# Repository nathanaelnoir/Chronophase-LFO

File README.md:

# Chronophase LFO

Chronophase LFO is a clock-synced Eurorack modulation source with an Arduino Nano core, four front-panel controls, one clock input, and separate unipolar, bipolar, and inverted bipolar outputs.

## Contents

- Overview
- Features
- Quick start (KiCad 9)
- Files
- Build & assembly notes
- Testing
- License & contributing

## Overview

This repository contains the KiCad 9 design files for Chronophase LFO, a clocked modulation module for Eurorack. An external clock drives the LFO core, the four main controls adjust `WAVEFORM`, `AMP`, `PHASE`, and `MODULATION`, and the output stage provides `UP_Out`, `BP_Out`, and `BP_Inv_Out` on separate jacks.

The current KiCad 9 project files are named `Synced_LFO`, and the top-level schematic title block still says `Clocked Modulation LFO`. The current documented revision for both the schematic and PCB is `v1.1`.

The hardware clearly includes an `Arduino_Nano_v3.x`, but there is no firmware source in this repository at the moment, only the hardware design files.

## Features

- Clock-synced LFO built around an `Arduino_Nano_v3.x` core and `TL072` output / shaping stages.
- Four front-panel controls: `WAVEFORM`, `AMP`, `PHASE`, and `MODULATION`.
- External `CLK In` jack for sync / clock input.
- Separate `UP_Out`, `BP_Out`, and `BP_Inv_Out` outputs.
- Front-panel activity LED.
- Standard Eurorack power distribution with `+12 V / -12 V / +5 V / GND` through a 16-pin Eurorack header sheet.
- Mixed build: SMD passives, diodes, electrolytics, and SOIC op-amps, with through-hole jacks, pots, LED, and Arduino Nano.

## Quick start

1. Install KiCad 9.
2. Open the project: `KiCad/Synced_LFO.kicad_pro`.
3. Review the top-level schematic and the `EURORACK_POWER` sheet, then run ERC/DRC before exporting manufacturing files.

## Files

- `KiCad/Synced_LFO.kicad_sch` - top-level schematic
- `KiCad/eurorack_power.kicad_sch` - Eurorack power sheet
- `KiCad/Synced_LFO.kicad_pcb` - PCB
- `KiCad/Synced_LFO.kicad_pro` - KiCad 9 project file
- `KiCad/Synced_LFO.kicad_prl` - local KiCad 9 project state
- `KiCad/Synced_LFO.sch` - legacy schematic file
- `KiCad/Synced_LFO.pro` - legacy project file

Note: there is a single PCB layout file (`KiCad/Synced_LFO.kicad_pcb`) for this project.

## Build & assembly notes

- Check orientation on the `Arduino_Nano_v3.x` module before soldering headers or the board directly. The USB end and pin order matter.
- Confirm pin-1 orientation on the `TL072` packages and polarity on the diodes and electrolytics before powering the board.
- Double-check the Eurorack power header orientation before applying power. This design uses `+12 V`, `-12 V`, `+5 V`, and `GND`, so a reversed cable is an easy way to damage parts.
- Panel hardware is straightforward but still substantial: four 100 k pots, four 3.5 mm jacks, and one LED.
- This is a mixed SMD + THT build, so it makes sense to solder the low-profile SMD parts first and leave the pots, jacks, LED, and Nano for later.

## Testing

1. Power the module from a current-limited Eurorack supply and verify `+12 V`, `-12 V`, `+5 V`, and `GND` on the power section before checking the rest of the circuit.
2. Feed a known clock into `CLK In` and confirm the front-panel LED shows activity.
3. Probe `UP_Out`, `BP_Out`, and `BP_Inv_Out` on a scope and confirm all three outputs are present and distinct.
4. Turn `WAVEFORM`, `AMP`, `PHASE`, and `MODULATION` through their full range and verify the outputs respond as expected.
5. If the Arduino Nano is fitted, confirm the module behavior is stable across different clock rates and after power-cycling.

## License & contributing

No `LICENSE` file has been added to this repository yet. Until that changes, assume the design is shared for reference, not under an explicit open-source license.

If a license is added later, this section can be updated properly.

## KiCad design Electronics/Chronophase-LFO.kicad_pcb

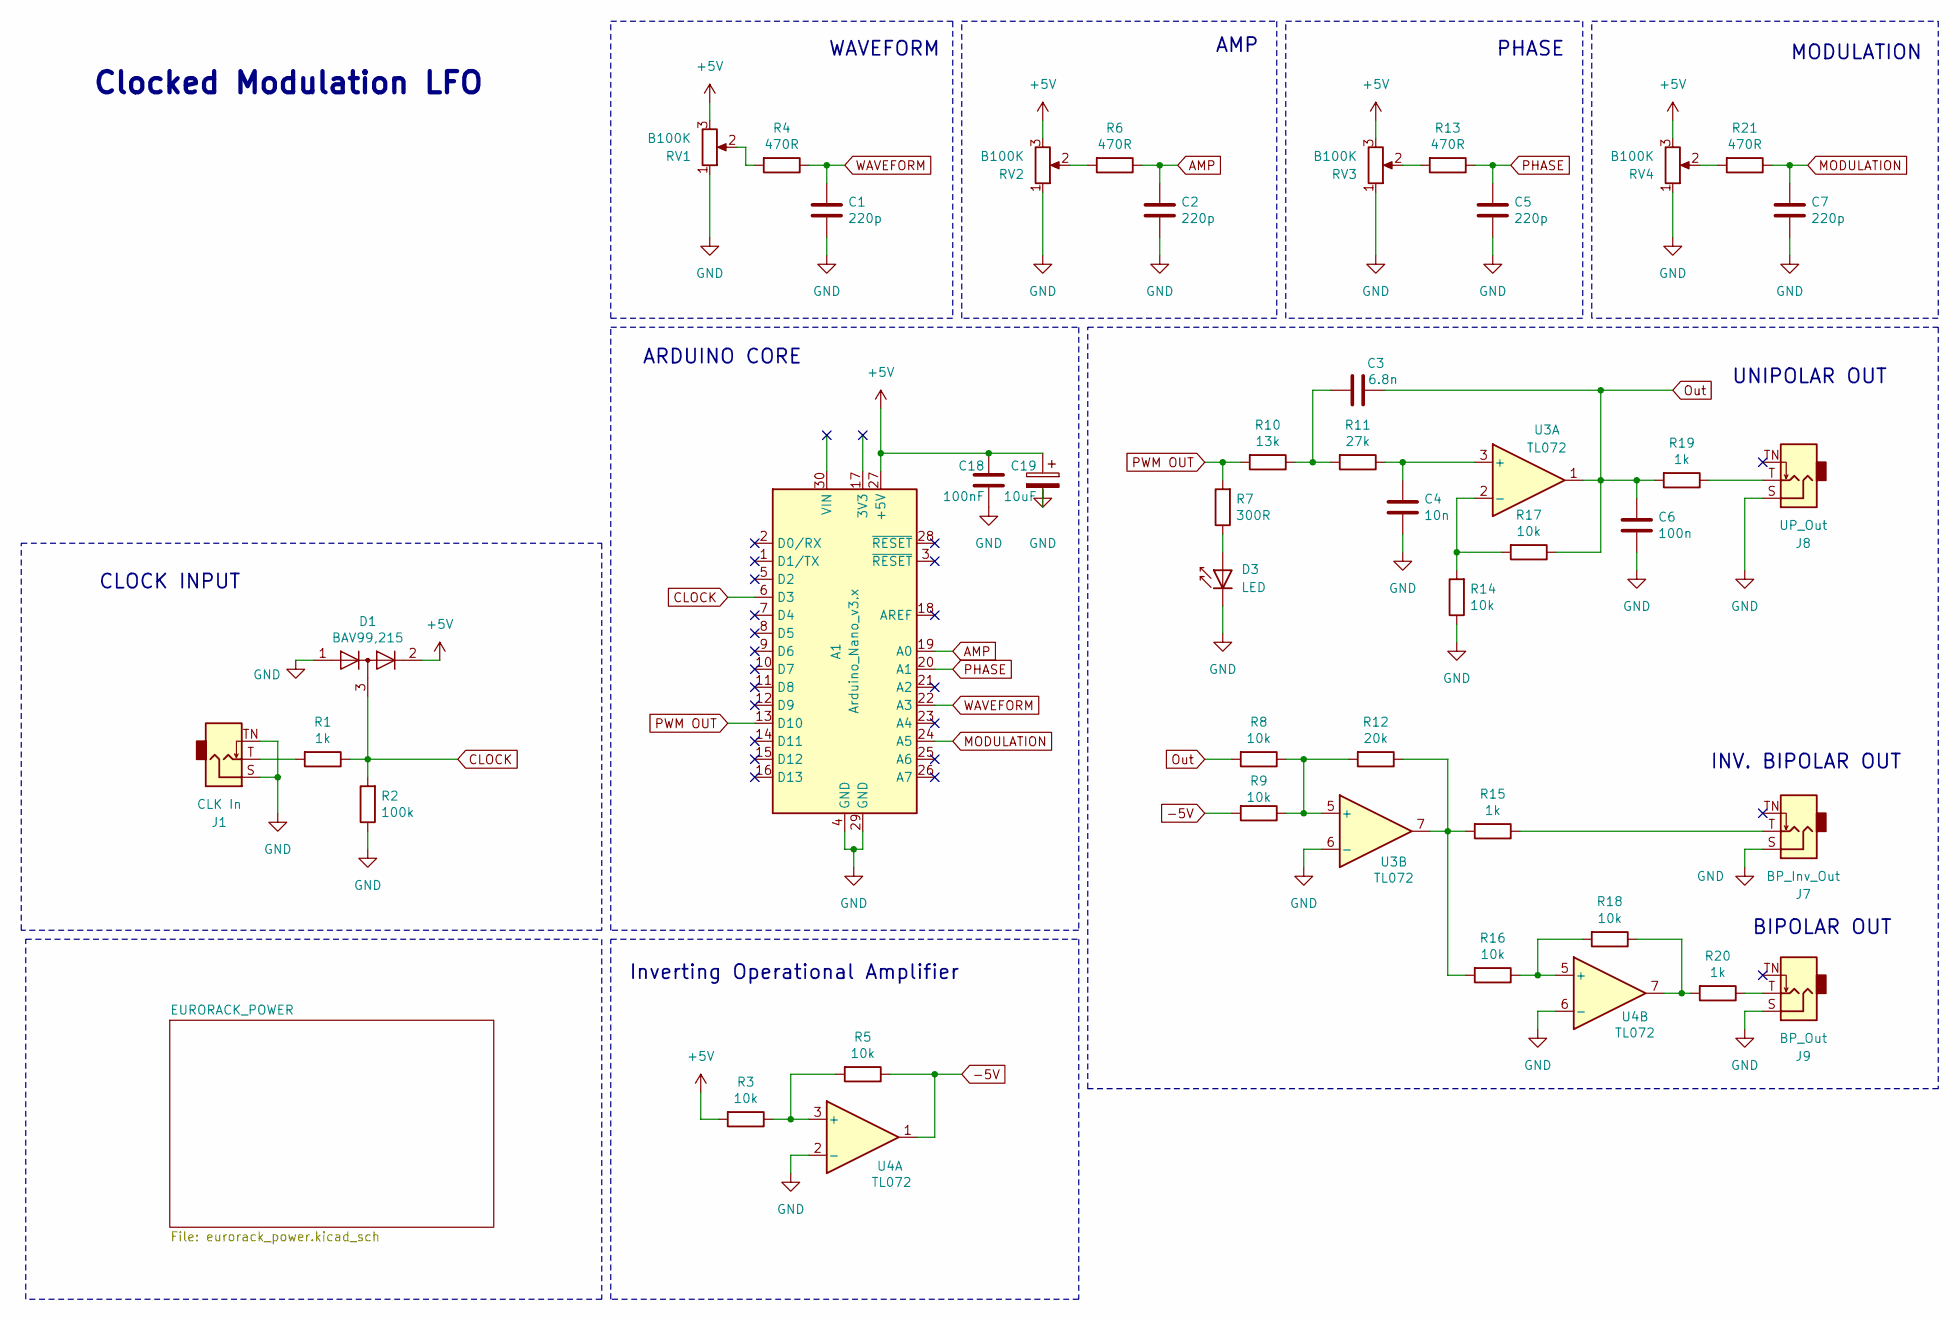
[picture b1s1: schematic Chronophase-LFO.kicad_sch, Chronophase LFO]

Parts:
A1: Arduino_Nano_v3.x; Arduino_Nano
C1, C2, C5, C7: 220p; C_0805_2012Metric_Pad1.18x1.45mm_HandSolder; LCSC C1530
C3: 6.8n; C_0805_2012Metric_Pad1.18x1.45mm_HandSolder; LCSC C1542
C4: 10n; C_0805_2012Metric_Pad1.18x1.45mm_HandSolder; LCSC C15195
C6: 100n; C_0805_2012Metric_Pad1.18x1.45mm_HandSolder; LCSC C1525
C18: 100nF; C_0805_2012Metric_Pad1.18x1.45mm_HandSolder
C19: 10uF; CP_Elec_5x5.4
D1: BAV99,215; SOT-23; LCSC C2500
D3: LED; LED_D3.0mm_Clear
J1: CLK In; Jack_3.5mm_QingPu_WQP-PJ398SM_Vertical
J7: BP_Inv_Out; Jack_3.5mm_QingPu_WQP-PJ398SM_Vertical
J8: UP_Out; Jack_3.5mm_QingPu_WQP-PJ398SM_Vertical
J9: BP_Out; Jack_3.5mm_QingPu_WQP-PJ398SM_Vertical
R1, R15, R19, R20: 1k; R_0805_2012Metric_Pad1.20x1.40mm_HandSolder; LCSC C11702
R2: 100k; R_0805_2012Metric_Pad1.20x1.40mm_HandSolder; LCSC C25741
R3, R5, R8, R9, R14, R16, R17, R18: 10k; R_0805_2012Metric_Pad1.20x1.40mm_HandSolder; LCSC C25744
R4, R6, R13, R21: 470R; R_0805_2012Metric_Pad1.20x1.40mm_HandSolder; LCSC C25117
R7: 300R; R_0805_2012Metric_Pad1.20x1.40mm_HandSolder; LCSC C25102
R10: 13k; R_0805_2012Metric_Pad1.20x1.40mm_HandSolder; LCSC C22797
R11: 27k; R_0805_2012Metric_Pad1.20x1.40mm_HandSolder; LCSC C25771
R12: 20k; R_0805_2012Metric_Pad1.20x1.40mm_HandSolder; LCSC C25765
RV1, RV2, RV3, RV4: B100K; Potentiometer_Alpha_RD901F_Vertical_Alt
U3, U4: TL072; SOIC-8_3.9x4.9mm_P1.27mm

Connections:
+5V: A1.27 (+5V), C18.1, C19.1, D1.2 (A), R3.2, RV1.3, RV2.3, RV3.3, RV4.3; also elsewhere on the board
-5V: R5.1, R9.2, U4.1
AMP: A1.19 (A0), C2.1, R6.1
CLOCK: A1.6 (D3), D1.3 (K), R1.1, R2.2
GND: A1.4 (GND), A1.29 (GND), C1.2, C2.2, C4.1, C5.2, C6.1, C7.2, C18.2, C19.2, D1.1 (K), D3.1 (K), J1.S, J1.TN, J7.S, J8.S, J9.S, R2.1, R14.1, RV1.1, RV2.1, RV3.1, RV4.1, U3.6 (-), U4.2 (-), U4.6 (-); also elsewhere on the board
MODULATION: A1.24 (A5), C7.1, R21.1
unnamed: C3.2, R10.1, R11.2
unnamed: D3.2 (A), R7.1
unnamed: J1.T, R1.2
unnamed: J7.T, R15.1
unnamed: J8.T, R19.1
unnamed: J9.T, R20.1
unnamed: R4.2, RV1.2
unnamed: R6.2, RV2.2
unnamed: R12.1, R15.2, R16.2, U3.7
unnamed: R13.2, RV3.2
unnamed: R18.1, R20.2, U4.7
unnamed: R21.2, RV4.2
unnamed: C4.2, R11.1, U3.3 (+)
unnamed: R14.2, R17.2, U3.2 (-)
unnamed: R8.1, R9.1, R12.2, U3.5 (+)
unnamed: R3.1, R5.2, U4.3 (+)
unnamed: R16.1, R18.2, U4.5 (+)
Out: C3.1, C6.2, R8.2, R17.1, R19.2, U3.1
PHASE: A1.20 (A1), C5.1, R13.1
PWM OUT: A1.13 (D10), R7.2, R10.2
WAVEFORM: A1.22 (A3), C1.1, R4.1

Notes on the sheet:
AMP
ARDUINO CORE
Clocked Modulation LFO
PHASE
WAVEFORM
MODULATION
INV. BIPOLAR OUT
BIPOLAR OUT
UNIPOLAR OUT
CLOCK INPUT
Inverting Operational Amplifier

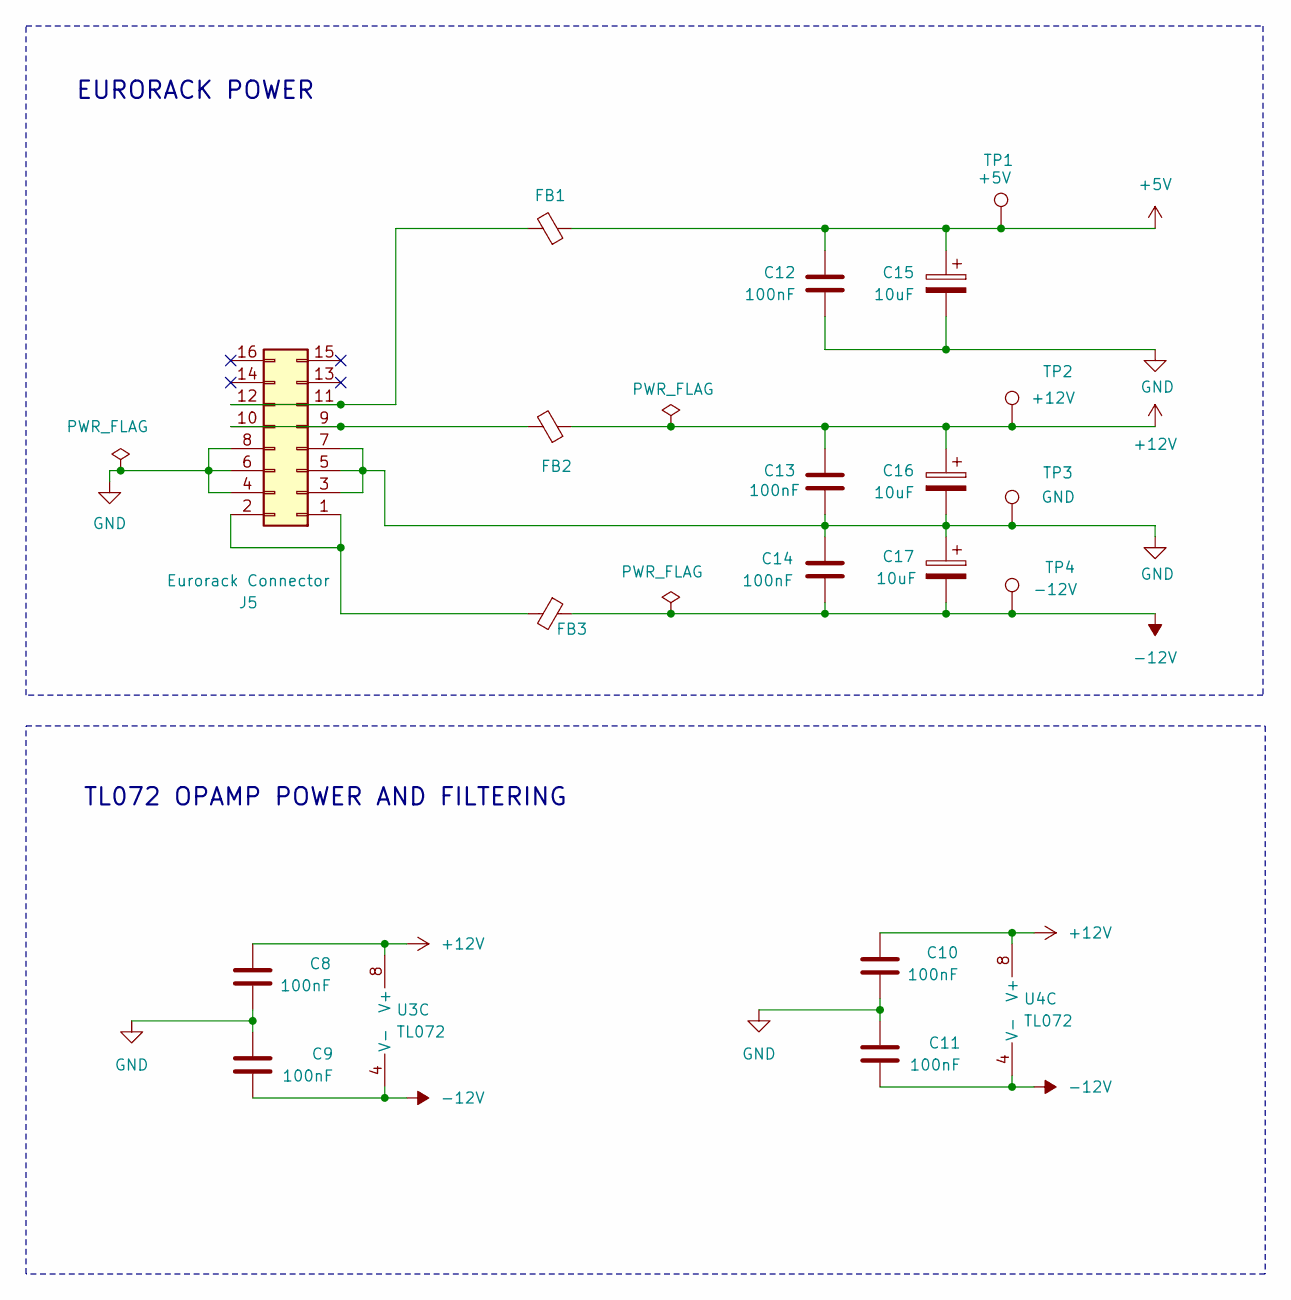
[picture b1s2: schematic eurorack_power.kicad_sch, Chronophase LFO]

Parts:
C8, C9, C10, C11, C12, C13, C14: 100nF; C_0805_2012Metric_Pad1.18x1.45mm_HandSolder
C15, C16, C17: 10uF; CP_Elec_5x5.4
FB1, FB2, FB3: FerriteBead_Small; L_0805_2012Metric_Pad1.05x1.20mm_HandSolder
J5: Eurorack Connector; IDC-Header_2x08_P2.54mm_Vertical
TP1: +5V; TestPoint_Pad_D1.5mm
TP2: +12V; TestPoint_Pad_D1.5mm
TP3: GND; TestPoint_Pad_D1.5mm
TP4: -12V; TestPoint_Pad_D1.5mm
U3, U4: TL072; SOIC-8_3.9x4.9mm_P1.27mm

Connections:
+5V: C12.1, C15.1, FB1.1, TP1.1; also elsewhere on the board
+12V: C8.1, C10.1, C13.1, C16.1, FB2.1, TP2.1, U3.8 (V+), U4.8 (V+)
-12V: C9.2, C11.2, C14.2, C17.2, FB3.1, TP4.1, U3.4 (V-), U4.4 (V-)
GND: C8.2, C9.1, C10.2, C11.1, C12.2, C13.2, C14.1, C15.2, C16.2, C17.1, J5.3, J5.4, J5.5, J5.6, J5.7, J5.8, TP3.1; also elsewhere on the board
unnamed: FB3.2, J5.1, J5.2
unnamed: FB2.2, J5.9, J5.10
unnamed: FB1.2, J5.11, J5.12

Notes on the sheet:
TL072 OPAMP POWER AND FILTERING
EURORACK POWER

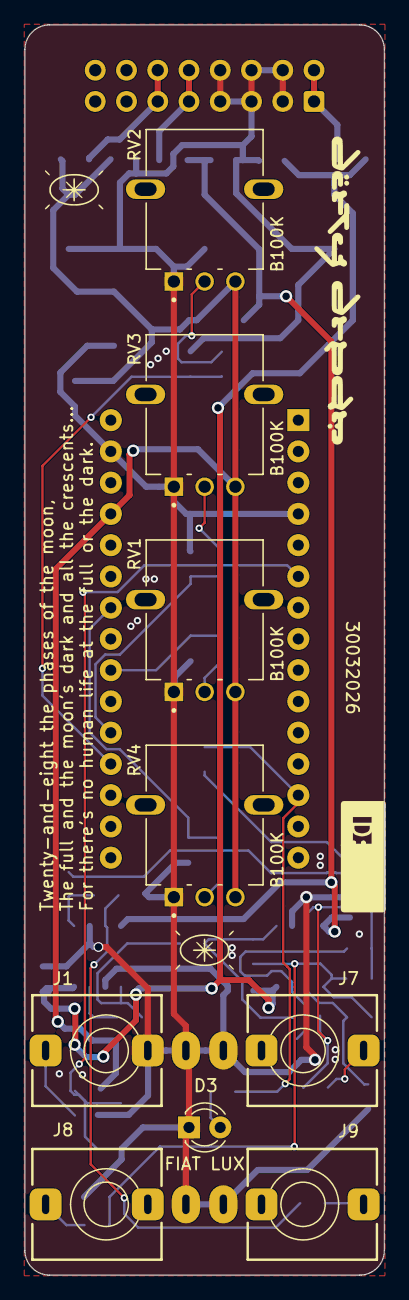
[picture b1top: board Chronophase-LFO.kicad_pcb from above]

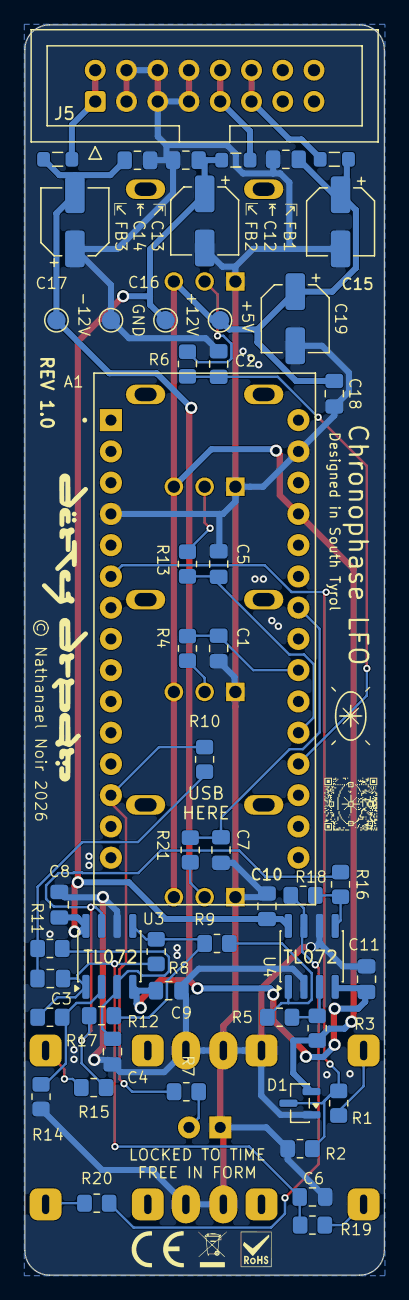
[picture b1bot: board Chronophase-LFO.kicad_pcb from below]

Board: 2 copper layers, 29.2 x 101.6 mm, 61 parts (52 on the bottom side), 32 nets.

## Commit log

2026-03-13 first commit message
2026-03-13 Added new Powerrail and fixed ERC Error
2026-03-25 chore(kicad): update project settings and board view state
2026-03-28 adding footprints
2026-03-28 adding last missing footprints
2026-03-29 fixing power in sch; placing components; connecting pads and coppering
2026-03-30 adding Logos on the pcb board
2026-03-30 docs: add Chronophase LFO README based on module template
2026-04-01 generating gerber files
2026-04-01 adding new logo
2026-04-02 changing folder names
2026-04-02 changing file names
2026-04-09 Updating to KiCad 10
2026-04-17 docs: update README revisions to v1.1 and add changelog for op-amp input fix
2026-04-17 fix: swapping the inputs of the opamps
2026-04-17 deleting the plot

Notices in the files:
Electronics/Chronophase-LFO.kicad_pcb:
© Nathanael Noir 2026
Electronics/Chronophase-LFO.kicad_sch:
© Dirty Dream – Nathanael Noir
README.md:
License: TBD
